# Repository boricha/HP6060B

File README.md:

# HP6060B
HP 6060B 3-60V/0-60A 300W SYSTEM DC ELECTRONIC LOAD  Graphic LCD Bridge

/*
 * $Id: main.c 3:06 PM 11/28/2019 ssk  $
 *
 * HP 6060B Graphic LCD .
 *
 * MIT License
 *
 * Copyright (c) 2019 ssk.
 *
 * Permission is hereby granted, free of charge, to any person obtaining a copy
 * of this software and associated documentation files (the "Software"), to deal
 * in the Software without restriction, including without limitation the rights
 * to use, copy, modify, merge, publish, distribute, sublicense, and/or sell
 * copies of the Software, and to permit persons to whom the Software is
 * furnished to do so, subject to the following conditions:
 *
 * The above copyright notice and this permission notice shall be included in all
 * copies or substantial portions of the Software.
 *
 * THE SOFTWARE IS PROVIDED "AS IS", WITHOUT WARRANTY OF ANY KIND, EXPRESS OR
 * IMPLIED, INCLUDING BUT NOT LIMITED TO THE WARRANTIES OF MERCHANTABILITY,
 * FITNESS FOR A PARTICULAR PURPOSE AND NONINFRINGEMENT. IN NO EVENT SHALL THE
 * AUTHORS OR COPYRIGHT HOLDERS BE LIABLE FOR ANY CLAIM, DAMAGES OR OTHER
 * LIABILITY, WHETHER IN AN ACTION OF CONTRACT, TORT OR OTHERWISE, ARISING FROM,
 * OUT OF OR IN CONNECTION WITH THE SOFTWARE OR THE USE OR OTHER DEALINGS IN THE
 * SOFTWARE.
 *
*/

<pre>
* The command was originally 10bits LSB First,
* but since the first 2 bits are always 0 and atmel SPI is 8bit system
* Accordingly 8Bits is used here
* +-----+--------------+------------------+---------------+
* |SYNC#|command field |10bit(originally) |8bit(used hear)|
* +-----+--------------+-----+------------+----------+----+
* |    0|Select LCD    |0x3f0|0b1111110000|0b11111100|0xfc|
* |    1|Unknown       |0x2e0|0b1011100000|0b10111000|0xb8|
* |    2|A Register    |0x028|0b0000101000|0b00001010|0x0a|
* |    3|B Register    |0x068|0b0001101000|0b00011010|0x1a|
* |    4|Annunciator   |0x2f0|0b1011110000|0b10111100|0xbc|
* |    5|C Register    |0x0a8|0b0010101000|0b00101010|0x2a|
* |    6|Display On/Off|0x320|0b1100100000|0b11001000|0xc8|
* +-----+--------------+------------------+---------------+
* Remembering that bits are transmitted from least significant bit (LSB) to most significant bit (MSB),
* aka. LSB First
</pre>

## Digial Waveform
        
## Message Frame Structure(MF)
   
## Modeling Event Based Behavior

## Schematics

## BOM(Bill of materials)
.png)
## PCB(top/bottom)
.png)
.png)
##
https://cafe.naver.com/carroty/337725
## Special thanks to: :+1: 
[LED display for HP 3457A multimeter - I did it :-)]<BR>
https://www.eevblog.com/forum/projects/led-display-for-hp-3457a-multimeter-i-did-it-)/ <BR>
I adapted this Aricle.  

述而不作.

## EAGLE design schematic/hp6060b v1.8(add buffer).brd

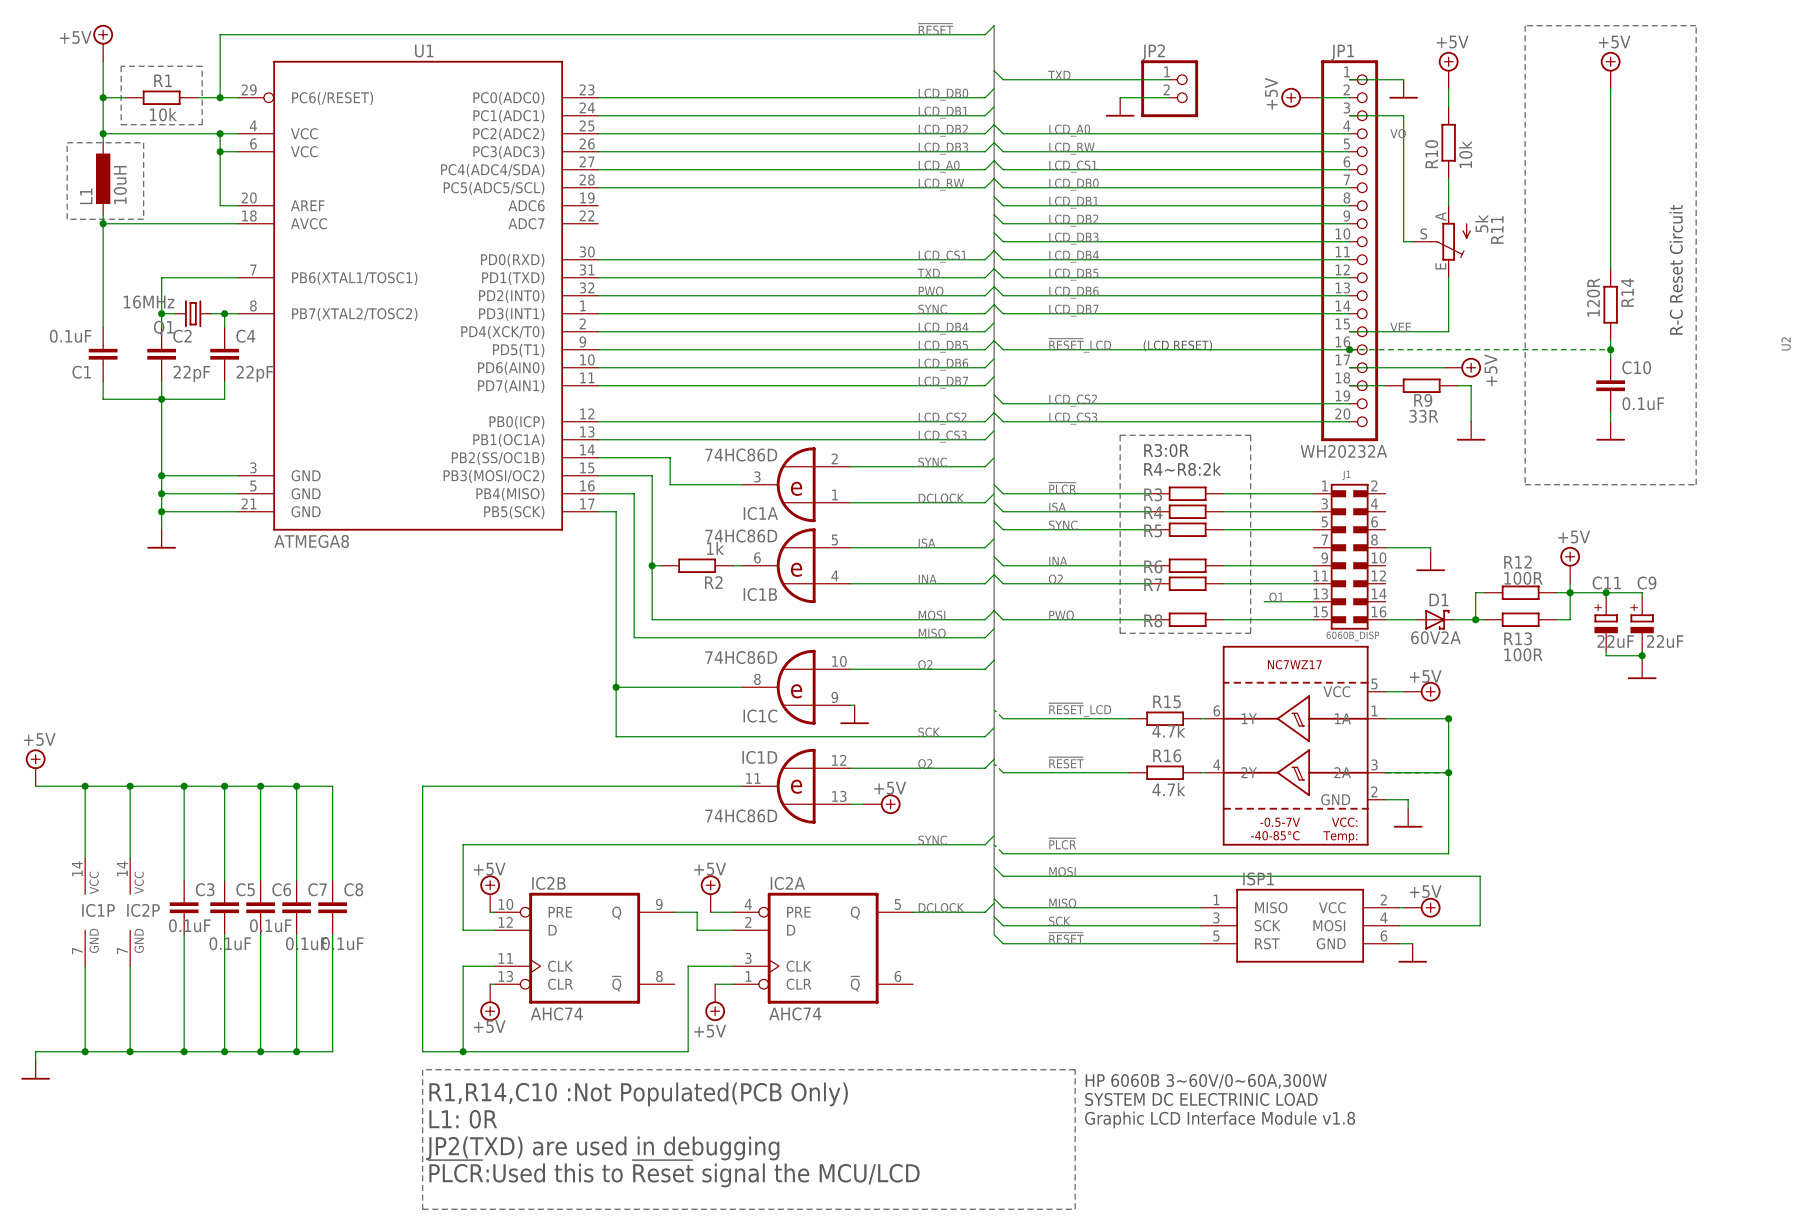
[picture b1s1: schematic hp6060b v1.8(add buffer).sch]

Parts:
C1, C3, C5: 0.1uF; C1206
C2, C4: 22pF; C0603
C6, C7, C8, C10: 0.1uF; C0805
C9, C11: 22uF; CT7343
D1: 60V2A; DIODE_SMB
IC1: 74HC86D; SO14
IC2: AHC74; TSSOP-14
ISP1: AVRISP-6; AVRISP
J1: 6060B_DISP; 61001621121
JP1: WH20232A; 1X20_ROUND
JP2: HEADER-1X2ROUND; 1X02_ROUND
L1: 10uH; L3225M
Q1: 16MHz; CSM-7X-DU
R1, R10: 10k; R1206
R2: 1k; R1206
R3: 0R; R1206
R4, R5, R6, R7, R8: 2k; R1206
R9: 33R; R2010
R11: 5k; B25P
R12, R13: 100R; R1206
R14: 120R; R0805
R15, R16: 4.7k; R0805
U1: ATMEGA8; LQFP32
U2: IC_BUFFER_NC7WZ17P6X; SOT65P210X110-6N

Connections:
!PLCR: R3.2, U2.1 (1A), U2.3 (2A)
!RESET: ISP1.5 (RST), R1.1, R16.1, U1.29 (PC6(/RESET))
!RESET!_LCD: C10.1, JP1.16, R14.2, R15.1
!SS: IC1.3 (O), U1.14 (PB2(SS/OC1B))
+5V: C3.1, C5.1, C6.1, C7.1, C8.1, C9.+, C11.+, IC1.13 (I1), IC1.14 (VCC), IC2.1 (CLR), IC2.4 (PRE), IC2.10 (PRE), IC2.13 (CLR), IC2.14 (VCC), ISP1.2 (VCC), JP1.2, JP1.17, L1.1, R1.2, R10.2, R12.2, R13.2, R14.1, U1.4 (VCC), U1.6 (VCC), U1.20 (AREF), U2.5 (VCC)
AVCC: C1.2, L1.2, U1.18 (AVCC)
DCLOCK: IC1.1 (I0), IC2.5 (Q)
GND: C1.1, C2.2, C3.2, C4.2, C5.2, C6.2, C7.2, C8.2, C9.-, C10.2, C11.-, IC1.7 (GND), IC1.9 (I0), IC2.7 (GND), ISP1.6 (GND), J1.8, JP1.1, JP2.2, R9.2, U1.3 (GND), U1.5 (GND), U1.21 (GND), U2.2 (GND)
INA: IC1.4 (I0), R6.1
ISA: IC1.5 (I1), R4.1
K: JP1.18, R9.1
LCD_A0: JP1.4, U1.27 (PC4(ADC4/SDA))
LCD_CS1: JP1.6, U1.30 (PD0(RXD))
LCD_CS2: JP1.19, U1.12 (PB0(ICP))
LCD_CS3: JP1.20, U1.13 (PB1(OC1A))
LCD_DB0: JP1.7, U1.23 (PC0(ADC0))
LCD_DB1: JP1.8, U1.24 (PC1(ADC1))
LCD_DB2: JP1.9, U1.25 (PC2(ADC2))
LCD_DB3: JP1.10, U1.26 (PC3(ADC3))
LCD_DB4: JP1.11, U1.2 (PD4(XCK/T0))
LCD_DB5: JP1.12, U1.9 (PD5(T1))
LCD_DB6: JP1.13, U1.10 (PD6(AIN0))
LCD_DB7: JP1.14, U1.11 (PD7(AIN1))
LCD_RW: JP1.5, U1.28 (PC5(ADC5/SCL))
MISO: ISP1.1 (MISO), U1.16 (PB4(MISO))
MOSI: ISP1.4 (MOSI), R2.2, U1.15 (PB3(MOSI/OC2))
unnamed: IC1.11 (O), IC2.3 (CLK), IC2.11 (CLK)
unnamed: D1.A (C), J1.16
unnamed: R10.1, R11.A
unnamed: J1.3, R4.2
unnamed: J1.5, R5.2
unnamed: D1.C (A), R12.1, R13.1
unnamed: R15.2, U2.6 (1Y)
unnamed: J1.9, R6.2
unnamed: J1.11, R7.2
unnamed: IC2.2 (D), IC2.9 (Q)
unnamed: J1.15, R8.2
unnamed: R16.2, U2.4 (2Y)
unnamed: IC1.6 (O), R2.1
unnamed: J1.1, R3.1
O1: J1.13
O2: IC1.10 (I1), IC1.12 (I0), R7.1
PWO: R8.1, U1.32 (PD2(INT0))
SCK: IC1.8 (O), ISP1.3 (SCK), U1.17 (PB5(SCK))
SYNC: IC1.2 (I1), IC2.12 (D), R5.1, U1.1 (PD3(INT1))
TXD: JP2.1, U1.31 (PD1(TXD))
VEE: JP1.15, R11.E
VO: JP1.3, R11.S
XTAL1: C2.1, Q1.2, U1.7 (PB6(XTAL1/TOSC1))
XTAL2: C4.1, Q1.1, U1.8 (PB7(XTAL2/TOSC2))

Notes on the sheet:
(LCD RESET)
R-C Reset Circuit
R1,R14,C10 :Not Populated(PCB Only) L1: 0R JP2(TXD) are used in debugging !PLCR!:Used this to !Reset! signal the MCU/LCD
HP 6060B 3~60V/0~60A,300W SYSTEM DC ELECTRINIC LOAD Graphic LCD Interface Module v1.8
R3:0R R4~R8:2k

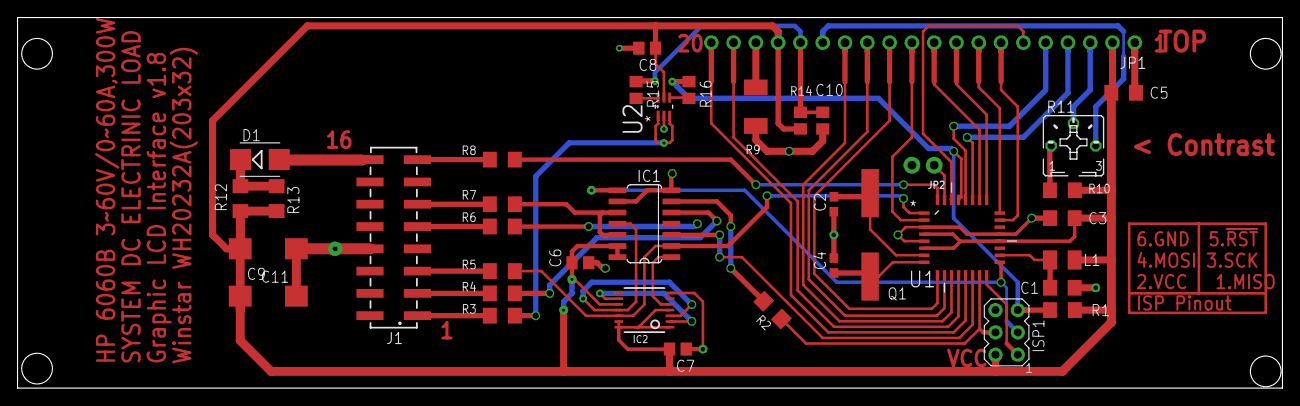
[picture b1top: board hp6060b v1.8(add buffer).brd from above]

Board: 2 copper layers, 144.1 x 42.2 mm, 38 parts (1 on the bottom side), 49 nets.

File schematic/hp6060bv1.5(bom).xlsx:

Bill of Materials
# | Parts | Device | Qty | Value | Package | Description
1 | C1 | C-EUC1206 | 1 | 0.1uF | C1206 | CAPACITOR, European symbol
2 | C2, C4 | C-EUC0603 | 2 | 22pF | C0603 | CAPACITOR, European symbol
3 | C3, C5, C8 | C-EUC1206 | 3 | 0.1uF | C1206 | CAPACITOR, European symbol
4 | C6, C7, C10 | C-EUC0805 | 3 | 0.1uF | C0805 | CAPACITOR, European symbol
5 | C9, C11 | CPOL-EUCT7343 | 2 | 22uF | CT7343 | POLARIZED CAPACITOR, European symbol
6 | D1 | SCHOTTKY-DIODE | 1 | 60V2A | DIODE_SMB | Schottky Diode
7 | H1, H2, H3, H4 | MOUNT-HOLE3.2 | 4 | MOUNT-HOLE3.2 | 3,2 | MOUNTING HOLE with drill center marker
8 | IC1 | 74HC86D | 1 | 74HC86D | SO14 | Quad 2-input EXCLUSIVE-OR (XOR) gate
9 | IC2 | IC_HC74 | 1 | AHC74 | TSSOP-14 | Dual D type positive edge triggered FLIP FLOP, preset and clear
10 | ISP1 | AVRISP-6 | 1 | AVRISP-6 | AVRISP | AVR ISP HEADER
11 | J1 | 6100XX21121_61001621121 | 1 | 6060B_DISP | 61001621121 | WR-PHD 2.54 mm SMT Dual Pin Header
12 | JP1 | HEADER-1X20ROUND | 1 | WH20232A | 1X20_ROUND
13 | JP2 | HEADER-1X2ROUND | 1 |  | 1X02_ROUND | PIN HEADER
14 | L1 | L-EUL3225M | 1 | 10uH | L3225M | INDUCTOR, European symbol
15 | Q1 | CSM-7X-DU | 1 | 16MHz | CSM-7X-DU | SMD CRYSTAL
16 | R1, R10 | R-EU_R1206 | 2 | 10k | R1206 | RESISTOR, European symbol
17 | R11 | TRIM_EU-B25P | 1 | 5k | B25P | POTENTIOMETER
18 | R12, R13 | R-EU_R1206 | 2 | 100R | R1206 | RESISTOR, European symbol
19 | R14 | R-EU_R0805 | 1 | 120R | R0805 | RESISTOR, European symbol
20 | R2 | R-EU_R1206 | 1 | 1k | R1206 | RESISTOR, European symbol
21 | R3 | R-EU_R1206 | 1 | 0R | R1206 | RESISTOR, European symbol
22 | R4, R5, R6, R7, R8 | R-EU_R1206 | 5 | 2k | R1206 | RESISTOR, European symbol
23 | R9 | R-EU_R1206 | 1 | 120R | R1206 | RESISTOR, European symbol
24 | U1 | IC_ATMEGA8 | 1 | IC_ATMEGA8 | LQFP32

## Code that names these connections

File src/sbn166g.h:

#ifndef SBN166G_H_
#define SBN166G_H_
/*
 * $Id: sbn166g_i2c.h 01:02 PM 2019-10-18 ssk  $
 *
 * Winstar WG20232A-TMI-V#A(202x32) LCD I2C(PCA9555) interface library.
 * Designed for AVANT SBN166G Dot-matrix STN LCD Driver with 32-row x 80-column
 *
 * MIT License
 *
 * Copyright (c) 2019 ssk.
 *
 * Permission is hereby granted, free of charge, to any person obtaining a copy
 * of this software and associated documentation files (the "Software"), to deal
 * in the Software without restriction, including without limitation the rights
 * to use, copy, modify, merge, publish, distribute, sublicense, and/or sell
 * copies of the Software, and to permit persons to whom the Software is
 * furnished to do so, subject to the following conditions:
 *
 * The above copyright notice and this permission notice shall be included in all
 * copies or substantial portions of the Software.
 *
 * THE SOFTWARE IS PROVIDED "AS IS", WITHOUT WARRANTY OF ANY KIND, EXPRESS OR
 * IMPLIED, INCLUDING BUT NOT LIMITED TO THE WARRANTIES OF MERCHANTABILITY,
 * FITNESS FOR A PARTICULAR PURPOSE AND NONINFRINGEMENT. IN NO EVENT SHALL THE
 * AUTHORS OR COPYRIGHT HOLDERS BE LIABLE FOR ANY CLAIM, DAMAGES OR OTHER
 * LIABILITY, WHETHER IN AN ACTION OF CONTRACT, TORT OR OTHERWISE, ARISING FROM,
 * OUT OF OR IN CONNECTION WITH THE SOFTWARE OR THE USE OR OTHER DEALINGS IN THE
 * SOFTWARE.
 *
*/
#define LCD_RST_PORT         PORTD
#define LCD_RST_DDR          DDRD
#define LCD_RST_PIN          1    // THE HARDWARE RESET IS EDGE-SENSITIVE. IT IS NOT LEVEL-SENSITIVE.

#define LCD_CONTROL_PORT     PORTC
#define LCD_CONTROL_DDR      DDRC
#define LCD_A0_PIN           4    // Instruction/Data select, H:D0-D7 are display data L:D0-D7 are control data
#define LCD_RW_PIN           5    // Read/Write control signal. L:Active (H:Read, L:Write)

#define LCD_CHIP1_PORT       PORTD
#define LCD_CHIP1_DDR        DDRD
#define LCD_CS1_PIN          0    // Enable signal (E) for the 68-type microcontroller

#define LCD_CHIP2_PORT       PORTB
#define LCD_CHIP2_DDR        DDRB
#define LCD_CS2_PIN          0    // Enable signal (E) for the 68-type microcontroller

#define LCD_CHIP3_PORT       PORTB
#define LCD_CHIP3_DDR        DDRB
#define LCD_CS3_PIN          1    // Enable signal (E) for the 68-type microcontroller

#define LCD_DATA_L_PORT      PORTC
#define LCD_DATA_L_DDR       DDRC // [0..3]
#define LCD_DATA_L_INPUT     PINC

#define LCD_DATA_H_PORT      PORTD 
#define LCD_DATA_H_DDR       DDRD // [4..7]
#define LCD_DATA_H_INPUT     PIND

#define LCD_CHIP1_START_X    0    // the CHIP1 start pixel of column
#define LCD_CHIP2_START_X    61   // the CHIP2 start pixel of column
#define LCD_CHIP3_START_X    141  // the CHIP3 start pixel of column
#define LCD_CHIP1_MAX_COL    61   // the CHIP1 max column of pixel
#define LCD_CHIP2_MAX_COL    140  // the CHIP2 max column of pixel
#define LCD_CHIP3_MAX_COL    201  // the CHIP3 max column of pixel

// command function equates for SBN166G LCD Display Controller
#define LCD_DISP_OFF         0xAE // turn LCD panel OFF
#define LCD_DISP_ON          0xAF // turn LCD panel ON
#define LCD_START_LINE       0xC0 // Specifies RAM line corresponding to top line of display.
#define LCD_SET_PAGE         0xB8 // set page address
#define LCD_SET_COL          0x00 // set column address
#define LCD_SET_ADC_NOR      0xA0 // Column/Segment Mapping Register,  set for normal direction
#define LCD_SET_ADC_REV      0xA1 // Column/Segment Mapping Register   set for reverse direction
#define LCD_STATIC_OFF       0xA4 // normal drive
#define LCD_STATIC_ON        0xA5 // static drive (power save)
#define LCD_DUTY_16          0xA8 // driving duty 1/16
#define LCD_DUTY_32          0xA9 // driving duty 1/32
#define LCD_SET_RMW_START    0xE0 // Read-Modify-Write
#define LCD_SET_RMW_END      0xEE // release the Read-Modify-Write
#define LCD_RESET            0xE2 // soft reset command

// Chip Select
#define LCD_CHIP_1           1
#define LCD_CHIP_2           2
#define LCD_CHIP_3           4
#define LCD_CHIP_ALL         7
#define LCD_RIGHT	         201  // the right most pixel        0 ~ 201
#define LCD_BOTTOM	         31   // the bottom of pixel         0 ~ 31

/* LCD screen and bitmap image array consants */
#define LCD_X_BYTES		    (LCD_RIGHT + 1)
#define LCD_Y_BYTES		    (LCD_BOTTOM + 1) / 8 // The number of Page (4page x 8bit = 32 pixels)

// Dot Color modes
#define LCD_DOT_CLR          0
#define LCD_DOT_SET          1
#define LCD_DOT_XOR          2

// AC timing for interface with a 68-type microcontroller at VDD=5 volts(unit:nano second)
#define LCD_tAS              0.02 // 20  tAS1,2:Address setup time with respect to R/W,C/S,C/D (ctrl line changes to E high)
#define LCD_tDS              0.08 // 80  Data setup time (Write data lines setup to dropping E)
#define LCD_tACC             0.90 // 90  Data access time(E high to valid read data)
#define LCD_tEWR             0.10 // 200 Enable pulse width READ(minimum E hi pulse width)
#define LCD_tEWW             0.08 // 160 Enable pulse width WRITE(minimum E hi pulse width)

typedef struct
{
  uint8_t x;
  uint8_t y;
} coordinates;

extern coordinates	_glcd_coord;

// function prototype
extern void glcd_init(void);
extern void glcd_clear(uint8_t fillchar);
extern void glcd_gotoxy(uint8_t x,  uint8_t y);
extern void glcd_offsetwrite(uint8_t data);
extern void glcd_bitmap(const uint8_t* bitmap, uint8_t x, uint8_t y,  const uint8_t color);
#endif
/*
* EOF
*/

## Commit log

2020-02-22 Create datasheet
2020-02-22 Create a
2020-02-22 Create bitmaps
2020-02-29 Create LICENSE

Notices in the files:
parts and their libraries:
Wurth_Connectors_WR-PHD: Copyright: Würth Elektronik
0microbuilder: This work is placed in the public domain, and may be freely used for commercial and non-commercial work with the following conditions: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
